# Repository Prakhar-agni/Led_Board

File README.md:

# Led_Board
The PCB design for a pair of LEDs that blink.
Project is made on EAGLE professional 6.3.0 . 
.sch file is to opened for schematic diagram.

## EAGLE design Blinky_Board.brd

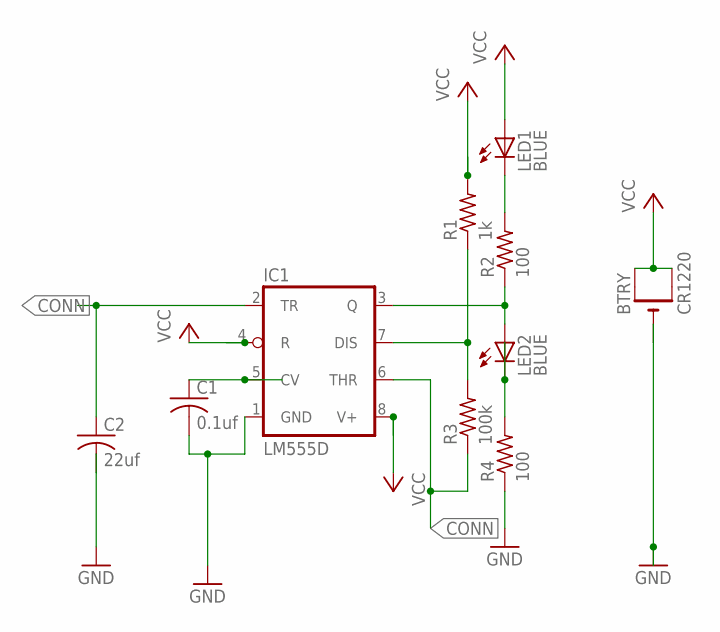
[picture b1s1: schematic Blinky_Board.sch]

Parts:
BTRY: CR1220; CR1220-SMD
C1: 0.1uf; C0805; MPN C0805X104J5RAC3316
C2: 22uf; C0805; MPN B32529C0224K000
IC1: LM555D; SO08; MPN NE555DR
LED1, LED2: BLUE; CHIPLED_0805; MPN MCL-S270SBLC
R1: 1k; R0805; MPN CRCW08051K00FKTA
R2, R4: 100; R0805; MPN ERJ-3EKF97R6V
R3: 100k; R0805; MPN CRCW0603100KFKEA

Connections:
CONN: C2.1, IC1.2 (TR), IC1.6 (THR), R3.1
GND: C1.2, C2.2, IC1.1 (GND), R4.1
unnamed: LED1.C, R2.2
unnamed: IC1.3 (Q), LED2.A, R2.1
unnamed: LED2.C, R4.2
unnamed: IC1.7 (DIS), R1.1, R3.2
unnamed: C1.1, IC1.5 (CV)
VCC: BTRY.+$1 (+), BTRY.+$2 (+1), IC1.4 (R), IC1.8 (V+), LED1.A, R1.2

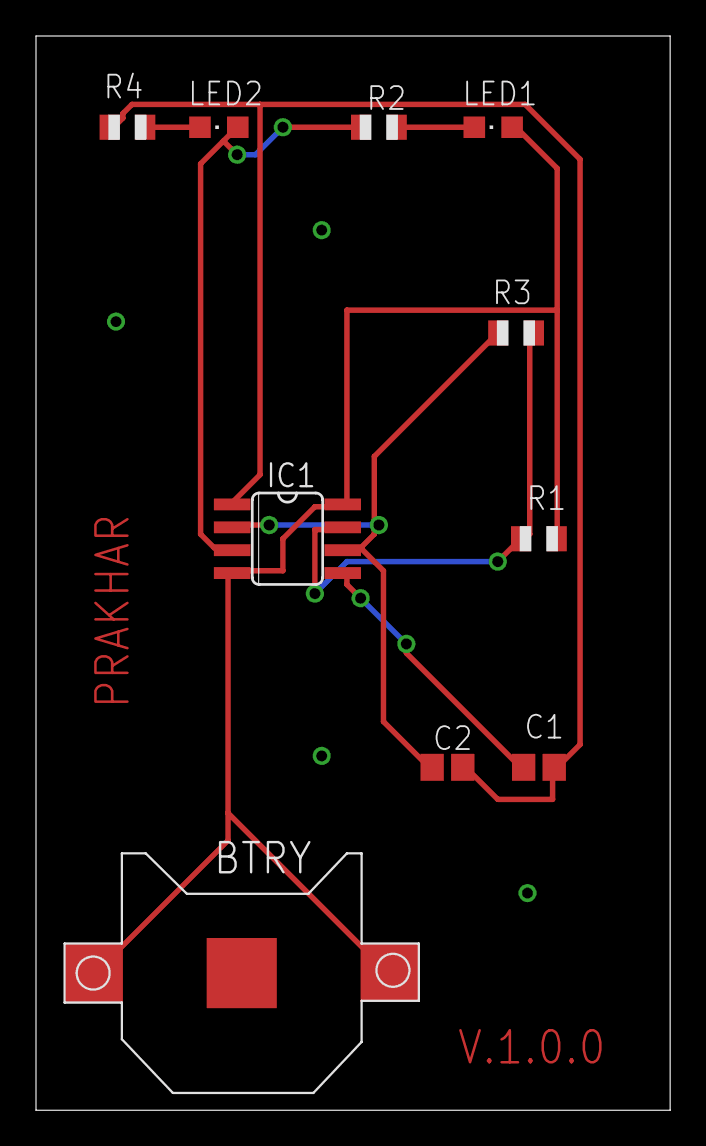
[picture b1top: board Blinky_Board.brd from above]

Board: 2 copper layers, 35.2 x 59.7 mm, 10 parts (0 on the bottom side), 8 nets.

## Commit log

2018-03-14 The complete design.
